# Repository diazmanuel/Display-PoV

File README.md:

# TD2-Project
Castro Germán.
Diaz Manuel.
Vieiro Alexis.

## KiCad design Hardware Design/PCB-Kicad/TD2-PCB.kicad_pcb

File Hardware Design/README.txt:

# Hardware Design

Hardware utilizado.

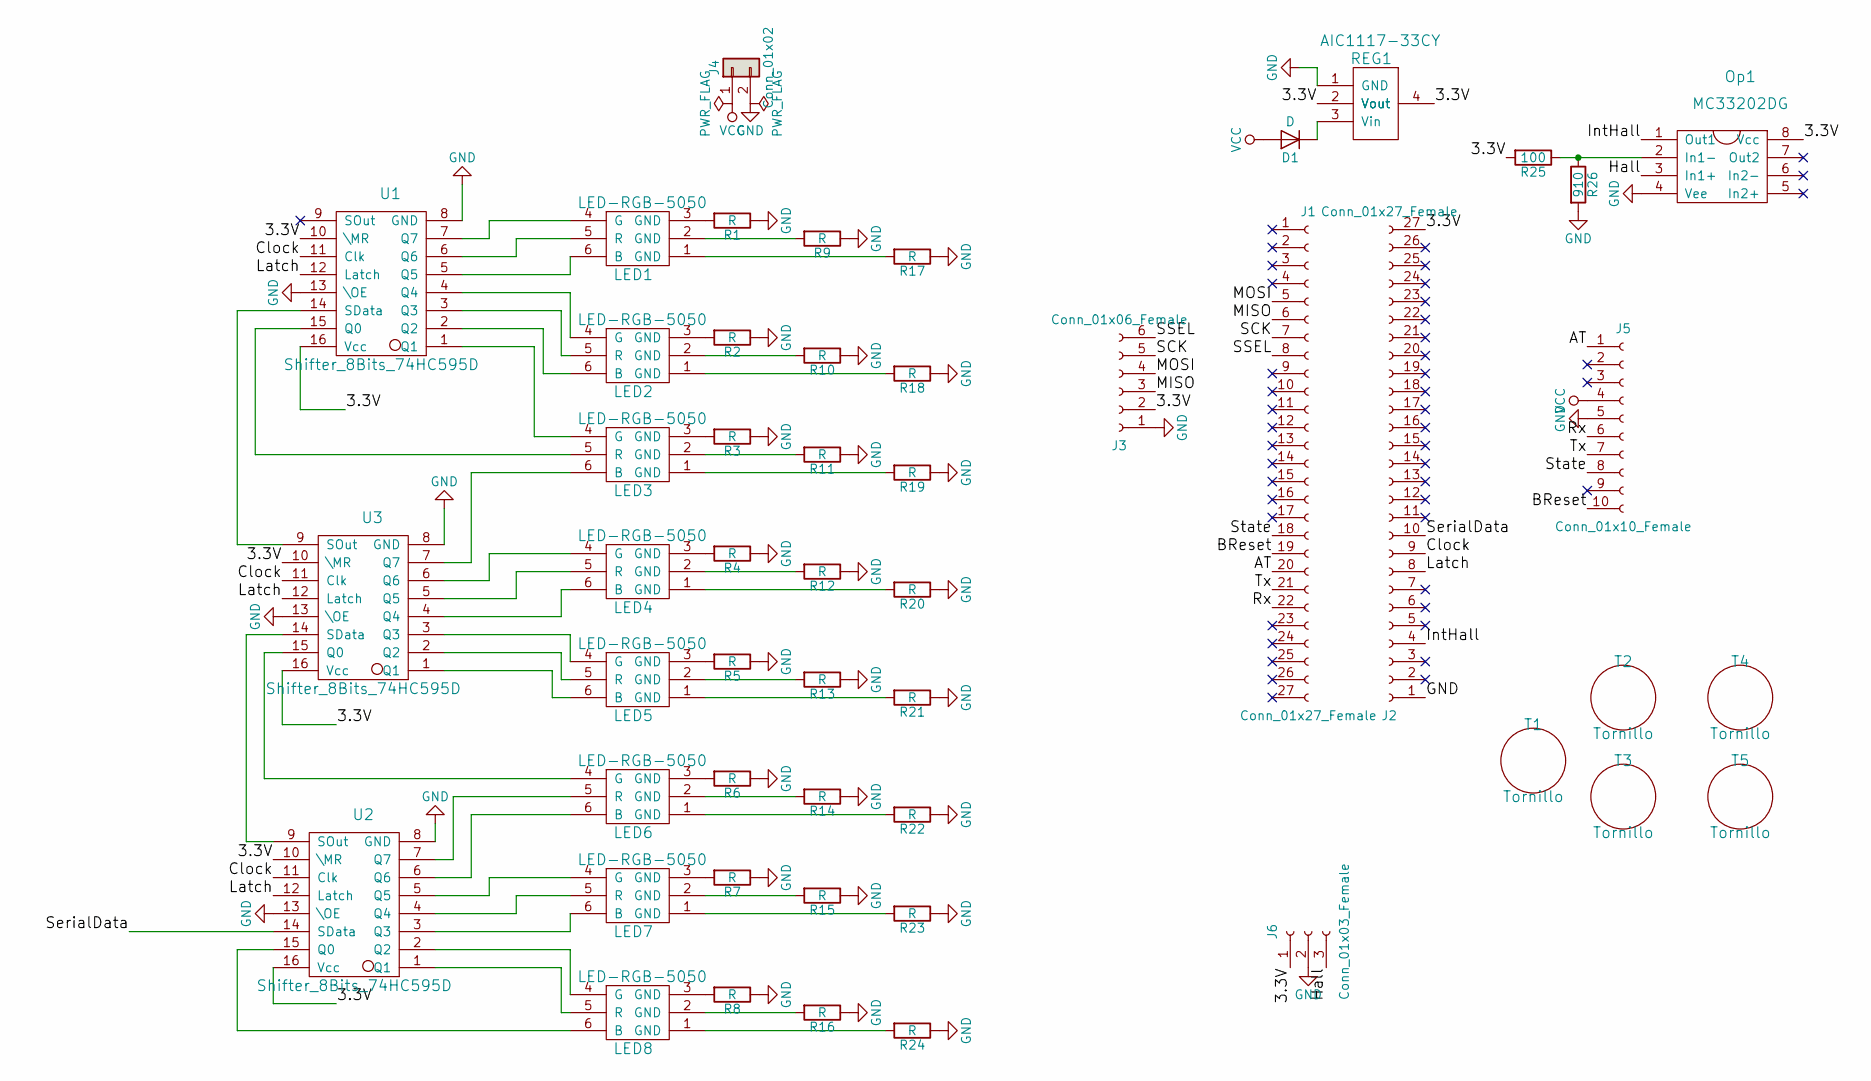
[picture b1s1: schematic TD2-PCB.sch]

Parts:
D1: D; DO-214AC
J1, J2: Conn_01x27_Female; Socket_Strip_Straight_1x27_Pitch2.54mm
J3: Conn_01x06_Female; Socket_Strip_Straight_1x06_Pitch2.54mm
J4: Conn_01x02; Pin_Header_Straight_1x02_Pitch2.54mm
J5: Conn_01x10_Female; Socket_Strip_Straight_1x10_Pitch2.54mm
J6: Conn_01x03_Female; Socket_Strip_Straight_1x03_Pitch2.54mm
LED1, LED2, LED3, LED4, LED5, LED6, LED7, LED8: LED-RGB-5050
Op1: MC33202DG
R1, R2, R3, R4, R5, R6, R7, R8, R9, R10, R11, R12, R13, R14, R15, R16, R17, R18, R19, R20, R21, R22, R23, R24: R; R_0805
R25: 100; R_0805
R26: 910; R_0805
REG1: AIC1117-33CY; AIC1117-33PT
T1, T2, T3, T4, T5: Tornillo; T3mm
U1, U2, U3: Shifter_8Bits_74HC595D

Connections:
/3.3V: J2.27, J3.2, J6.1, Op1.8 (Vcc), R25.2, REG1.2 (Vout), REG1.4 (Vout), U1.10 (\MR), U1.16 (Vcc), U2.10 (\MR), U2.16 (Vcc), U3.10 (\MR), U3.16 (Vcc)
/AT: J1.20, J5.1
/BReset: J1.19, J5.10
/Clock: J2.9, U1.11 (Clk), U2.11 (Clk), U3.11 (Clk)
/Hall: J6.3, Op1.3 (In1+)
/IntHall: J2.4, Op1.1 (Out1)
/Latch: J2.8, U1.12 (Latch), U2.12 (Latch), U3.12 (Latch)
/MISO: J1.6, J3.3
/MOSI: J1.5, J3.4
/Rx: J1.22, J5.6
/SCK: J1.7, J3.5
/SSEL: J1.8, J3.6
/SerialData: J2.10, U2.14 (SData)
/State: J1.18, J5.8
/Tx: J1.21, J5.7
GND: J2.1, J3.1, J4.2, J5.5, J6.2, Op1.4 (Vee), R1.1, R2.1, R3.1, R4.1, R5.1, R6.1, R7.1, R8.1, R9.1, R10.1, R11.1, R12.1, R13.1, R14.1, R15.1, R16.1, R17.1, R18.1, R19.1, R20.1, R21.1, R22.1, R23.1, R24.1, R26.2, REG1.1 (GND), U1.8 (GND), U1.13 (\OE), U2.8 (GND), U2.13 (\OE), U3.8 (GND), U3.13 (\OE)
unnamed: D1.1 (K), REG1.3 (Vin)
unnamed: LED1.1 (GND), R17.2
unnamed: LED1.2 (GND), R9.2
unnamed: LED1.3 (GND), R1.2
unnamed: LED1.4 (G), U1.7 (Q7)
unnamed: LED1.5 (R), U1.6 (Q6)
unnamed: LED1.6 (B), U1.5 (Q5)
unnamed: LED2.1 (GND), R18.2
unnamed: LED2.2 (GND), R10.2
unnamed: LED2.3 (GND), R2.2
unnamed: LED2.4 (G), U1.4 (Q4)
unnamed: LED2.5 (R), U1.3 (Q3)
unnamed: LED2.6 (B), U1.2 (Q2)
unnamed: LED3.1 (GND), R19.2
unnamed: LED3.2 (GND), R11.2
unnamed: LED3.3 (GND), R3.2
unnamed: LED3.4 (G), U1.1 (Q1)
unnamed: LED3.5 (R), U1.15 (Q0)
unnamed: LED3.6 (B), U3.7 (Q7)
unnamed: LED4.1 (GND), R20.2
unnamed: LED4.2 (GND), R12.2
unnamed: LED4.3 (GND), R4.2
unnamed: LED4.4 (G), U3.6 (Q6)
unnamed: LED4.5 (R), U3.5 (Q5)
unnamed: LED4.6 (B), U3.4 (Q4)
unnamed: LED5.1 (GND), R21.2
unnamed: LED5.2 (GND), R13.2
unnamed: LED5.3 (GND), R5.2
unnamed: LED5.4 (G), U3.3 (Q3)
unnamed: LED5.5 (R), U3.2 (Q2)
unnamed: LED5.6 (B), U3.1 (Q1)
unnamed: LED6.1 (GND), R22.2
unnamed: LED6.2 (GND), R14.2
unnamed: LED6.3 (GND), R6.2
unnamed: LED6.4 (G), U3.15 (Q0)
unnamed: LED6.5 (R), U2.7 (Q7)
unnamed: LED6.6 (B), U2.6 (Q6)
unnamed: LED7.1 (GND), R23.2
unnamed: LED7.2 (GND), R15.2
unnamed: LED7.3 (GND), R7.2
unnamed: LED7.4 (G), U2.5 (Q5)
unnamed: LED7.5 (R), U2.4 (Q4)
unnamed: LED7.6 (B), U2.3 (Q3)
unnamed: LED8.1 (GND), R24.2
unnamed: LED8.2 (GND), R16.2
unnamed: LED8.3 (GND), R8.2
unnamed: LED8.4 (G), U2.2 (Q2)
unnamed: LED8.5 (R), U2.1 (Q1)
unnamed: LED8.6 (B), U2.15 (Q0)
unnamed: Op1.2 (In1-), R25.1, R26.1
unnamed: U1.14 (SData), U3.9 (SOut)
unnamed: U2.9 (SOut), U3.14 (SData)
VCC: D1.2 (A), J4.1, J5.4

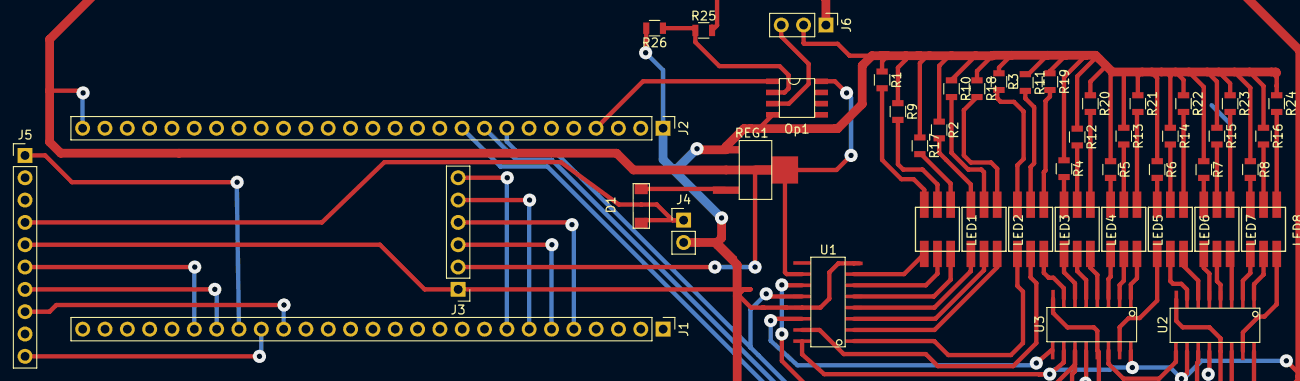
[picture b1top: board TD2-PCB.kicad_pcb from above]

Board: 2 copper layers, 51 parts (0 on the bottom side), 69 nets.

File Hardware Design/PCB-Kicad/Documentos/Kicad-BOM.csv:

"Date:,""30/08/2018 12:55:25"""
"Ref,""Qnty"",""Value"",""Cmp name"",""Footprint"",""Description"",""Vendor"""



"D1, ,""1"",""D"",""D"",""TD2-Componentes:DO-214AC"",""Diode"","""""
"J1, J2, ,""2"",""Conn_01x27_Female"",""Conn_01x27_Female"",""Socket_Strips:Socket_Strip_Straight_1x27_Pitch2.54mm"",""Generic connector, single row, 01x27"","""""
"J3, ,""1"",""Conn_01x06_Female"",""Conn_01x06_Female"",""Socket_Strips:Socket_Strip_Straight_1x06_Pitch2.54mm"",""Generic connector, single row, 01x06"","""""
"J4, ,""1"",""Conn_01x02"",""Conn_01x02"",""Pin_Headers:Pin_Header_Straight_1x02_Pitch2.54mm"",""Generic connector, single row, 01x02"","""""
"J5, ,""1"",""Conn_01x10_Female"",""Conn_01x10_Female"",""Socket_Strips:Socket_Strip_Straight_1x10_Pitch2.54mm"",""Generic connector, single row, 01x10"","""""
"J6, ,""1"",""Conn_01x03_Female"",""Conn_01x03_Female"",""Socket_Strips:Socket_Strip_Straight_1x03_Pitch2.54mm"",""Generic connector, single row, 01x03"","""""
"LED1, LED2, LED3, LED4, LED5, LED6, LED7, LED8, ,""8"",""LED-RGB-5050"",""LED-RGB-5050"",""TD2-Componentes:LED-RGB-5050"","""","""""
"Op1, ,""1"",""MC33202DG"",""MC33202DG"",""TD2-Componentes:MC33202DG"","""","""""
"R2, R10, R18, R1, R9, R17, R3, R11, R19, R4, R12, R20, R5, R13, R21, R6, R14, R22, R7, R15, R23, R8, R16, R24, ,""24"",""R"",""R"",""Resistors_SMD:R_0805"",""Resistor"","""""
"R25, ,""1"",""100"",""R"",""Resistors_SMD:R_0805"",""Resistor"","""""
"R26, ,""1"",""910"",""R"",""Resistors_SMD:R_0805"",""Resistor"","""""
"REG1, ,""1"",""AIC1117-33CY"",""AIC1117-33CY"",""TD2-Componentes:AIC1117-33PT"","""","""""
"T4, T5, T2, T3, T1, ,""5"",""Tornillo"",""Tornillo"",""TD2-Componentes:T3mm"","""","""""
"U1, U2, U3, ,""3"",""Shifter_8Bits_74HC595D"",""Shifter_8Bits_74HC595D"",""TD2-Componentes:Shifter_8Bits_74HC595D"","""","""""

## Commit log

2018-05-05 Pieza 3D SolidWorks
    pieza 3d giratoria
2018-05-07 Adding new files
2018-05-07 pieza 3d formato impresora 3d (#2)
2018-05-16 Agrego Plantilla de Proyecto tipo
2018-05-21 uart + pc + datasheet (#3)
    Merge branch3 - diazmanuel
2018-05-28 Branch3 (#6)
    * uart + pc + datasheet
    * cargadata
    * bluetooth init
2018-05-29 Branch4 (#7)
    * uart + pc + datasheet
    * cargadata
    * bluetooth init
    * codigo unificado
2018-06-07 Branch4 (#8)
    * uart + pc + datasheet
    * cargadata
    * bluetooth init
    * codigo unificado
    * aun no funciona
    * test+datasheets
2018-06-07 Limpio archivos de debug (#9)
2018-06-16 My branch (#11)
    * Limpio archivos de debug
    * 06/07/18 Code Update
    * gitignore Update
    * 06/07/18 Code Update
    * 06/07/18 Update
    * Update
2018-06-16 Branch4 (#10)
    * Limpio archivos de debug
    * 06/07/18 Code Update
    * gitignore Update
    * 06/07/18 Code Update
    * 06/07/18 Update
    * Update
2018-06-16 README add (#12)
2018-07-03 AUR9713
2018-08-16 placa final td2
2018-08-16 se fue
2018-08-16 este tambien
2018-08-16 pieazas 3d
2018-08-17 y este tambien
2018-08-17 add hojas de datos
    aca va chamuyo~
2018-08-27 Delete CAMtastic1.Cam
    viejo
2018-08-27 Delete CAMtastic2.Cam
    viejo
2018-08-27 Delete PCB_TPO_TD2.PDF
    viejo
2018-08-27 Delete PCB_TPO_TD2.rar
    viejo
2018-08-31 Alex (#13)
    * Add files via upload
    +PCB Kicad
    * Add files via upload
    * Add files via upload
    * Delete PCB-Kicad.zip
2018-09-06 nuevo inductor
2018-11-15 Hardware Update(#28)
2018-12-03 Informes (#30)
2018-12-08 manual de usuario (#32)
2018-12-11 Diaz (#34)
    * elimino codigo viejo
    * informesPDF
2018-12-11 My branch (#39)
    * Agrego migracion de proyecto a FreeRTOS
    * Agrego migracion de proyecto a FreeRTOS
    * Code Update
    * Drivers Update: Peek & Overwrite (#14)
    * Limpio uso de queues (#15)
    * My branch (#16)
2018-12-11 ultimo informe
2018-12-11 Agrego Documentacion
    Doxygen
2018-12-28 Firmware sin O.S.
